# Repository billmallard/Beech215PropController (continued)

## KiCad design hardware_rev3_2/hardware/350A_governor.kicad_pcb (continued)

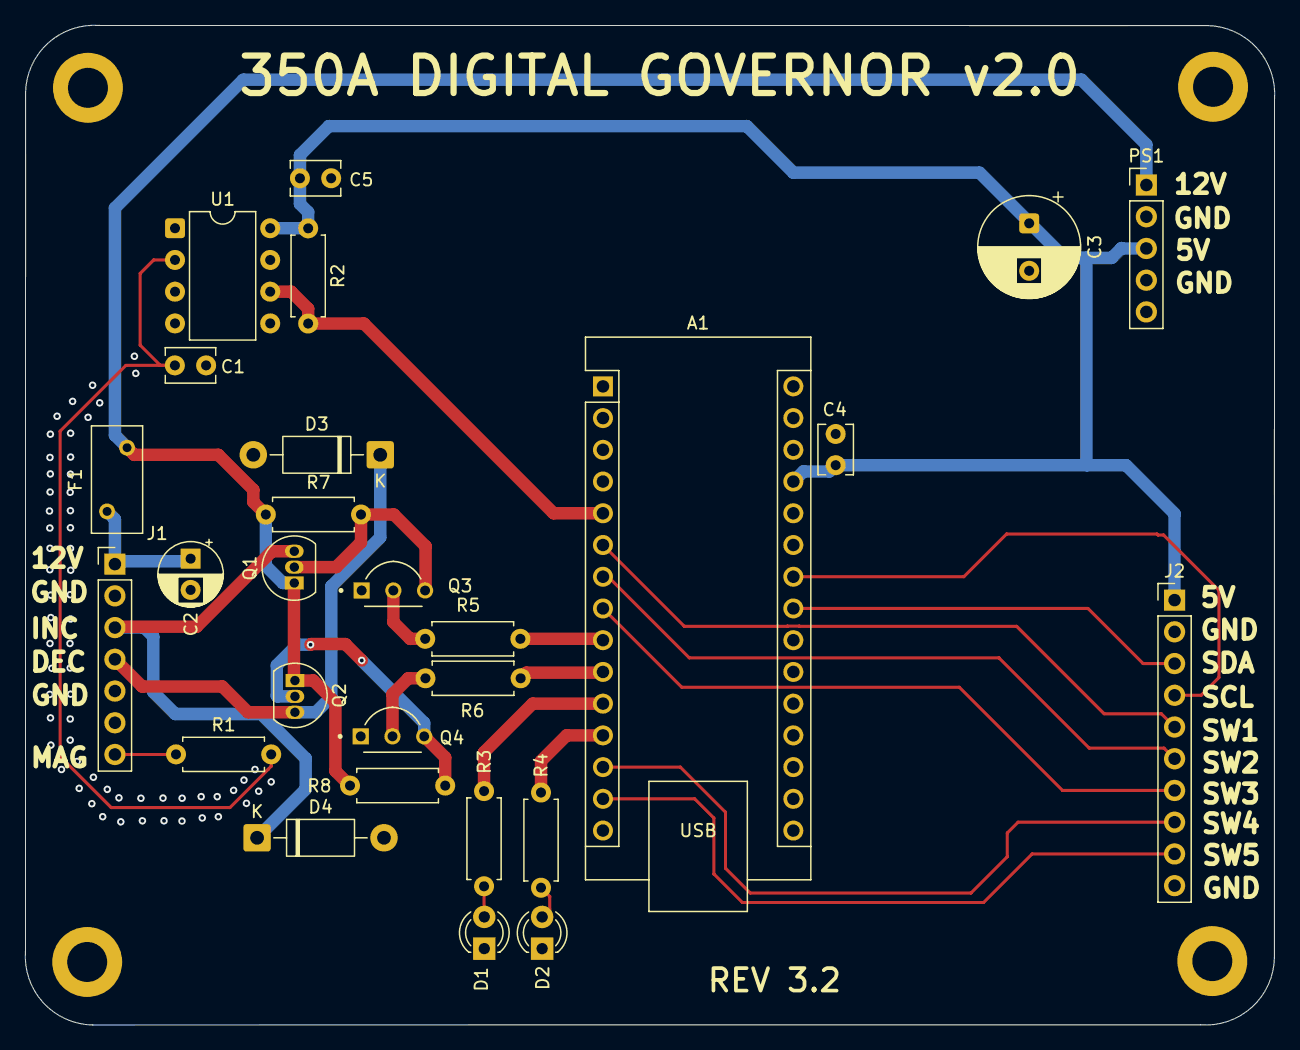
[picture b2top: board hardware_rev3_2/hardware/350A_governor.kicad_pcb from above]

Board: 2 copper layers, 100.0 x 80.0 mm, 27 parts (0 on the bottom side), 26 nets.

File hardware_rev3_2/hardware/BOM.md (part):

# Bill of Materials — Rev 3.2

Complete parts list for one governor build. All parts available from Digi-Key, Mouser, or Amazon.
Links are to Digi-Key where possible — they're reliable, stock everything, and ship fast.

**Estimated total cost: $60–100** depending on sourcing (Amazon vs. Digi-Key, bulk vs. singles)

---

## PCB

| Item | Specification | Qty | Source | Est. Cost | Notes |
|---|---|---|---|---|---|
| Governor PCB | 100×80mm 2-layer FR4 | 5 | JLCPCB | ~$2 + shipping | Upload `gerbers/350A_governor_JLCPCB.zip`; default settings; you get 5, use 1 |

**JLCPCB order settings:**
- Base Material: FR4
- Layers: 2
- PCB Thickness: 1.6mm
- Surface Finish: HASL (with lead) — cheapest and fine for this application
- Copper Weight: 1oz
- Everything else: defaults

---

## ICs and Active Components

| Ref | Part | Description | Digi-Key PN | Qty | Est. Cost | Notes |
|---|---|---|---|---|---|---|
| A1 | Arduino Nano (ATmega328P) | Microcontroller | — | 1 | $4–8 | Buy the CH340 version (most common on Amazon/eBay). Avoid Nano Every — different pinout. |
| U1 | 6N137 | High-speed optocoupler | 516-2878-5-ND | 1 | $0.60 | DIP-8. Do not substitute 4N25/4N35 — too slow for mag pulses. |
| PS1 | LM2596S-5V Module | DC-DC 5V switching regulator | — | 1 | $1–3 | Pre-built module. **Must be labeled "5V" not adjustable.** Verify output before installing. Available on Amazon, 10-packs for $8. |
| OLED | SSD1306 1.3" OLED | I2C display 128×64 | — | 1 | $6–10 | Must be I2C (2-wire), 128×64. Many on Amazon. Verify module is 4-pin (VCC/GND/SCL/SDA). |

---

## Transistors — High-Side Relay Driver

Two-channel NPN+PNP circuit replacing the ULN2003A from Rev 2. All TO-92 package.

| Ref | Part | Type | Digi-Key PN | Qty | Est. Cost | Notes |
|---|---|---|---|---|---|---|
| Q1, Q2 | 2N2907A | PNP — high-side switch | 2N2907A-ND | 2 | ~$0.50 ea | TO-92L. Switches +12V to relay coil. |
| Q3, Q4 | 2N2222A | NPN — level shifter | 2N2222A-ND | 2 | ~$0.30 ea | TO-92. Driven by Nano 5V logic. |

---

## Passives — Resistors

All resistors: 1/4W metal film, 1% tolerance

| Ref | Value | Digi-Key PN | Qty | Notes |
|---|---|---|---|---|
| R1 | 10kΩ | 10KEBK-ND | 1 | Magneto input current limit |
| R2 | 4.7kΩ | 4.7KEBK-ND | 1 | Optocoupler pull-up |
| R3, R4 | 330Ω | 330EBK-ND | 2 | LED current limiters |
| R5, R6 | 1kΩ | 1.0KEBK-ND | 2 | NPN base resistors (Q3, Q4) |
| R7, R8 | 10kΩ | 10KEBK-ND | 2 | PNP base pull-up to +12V (Q1, Q2) |

**Tip:** R1, R7, R8 are all 10kΩ — order 4 total on a single line item.

---

## Passives — Capacitors

| Ref | Value | Type | Digi-Key PN | Qty | Notes |
|---|---|---|---|---|---|
| C1, C4, C5 | 100nF (0.1µF) | Ceramic disc | 445-173-ND | 3 | Non-polarized; marked "104" |
| C2 | 100µF 25V | Electrolytic | 493-1215-ND | 1 | **POLARIZED** — observe polarity. 12V input bulk cap. |
| C3 | 47µF 10V | Electrolytic | 493-1205-ND | 1 | **POLARIZED** — observe polarity. 5V output filter cap. |

---

## Protection — Diodes and Fuse

| Ref | Part | Digi-Key PN | Qty | Notes |
|---|---|---|---|---|
| D3, D4 | 1N4001 | 1N4001FSCT-ND | 2 | Flyback diodes across each relay coil circuit — clamp the coil's inductive spike when the PNP switches off. **Do not omit.** Polarity: cathode (band) to the relay output pad (marked "K" on silkscreen), anode to ground. |
| F1 | 1A PTC resettable fuse | — | 1 | In series with +12V_RAW input. Self-resets after overcurrent. Belkin/Bel Fuse 0ZRE or equivalent. |

---

## Indicators

| Ref | Part | Digi-Key PN | Qty | Notes |
|---|---|---|---|---|
| D1 | 3mm Red LED | 754-1264-ND | 1 | Standard brightness; INC indicator |
| D2 | 3mm Green LED | 754-1221-ND | 1 | Standard brightness; DEC indicator |

---

## Connectors and Sockets

| Ref | Part | Qty | Notes |
|---|---|---|---|
| — | DIP-8 socket | 1 | For U1 (6N137). Use machined-pin (turned-pin) type for reliability. |
| — | 15-pin female single-row socket strip | 2 | For Arduino Nano. Cut to length or buy pre-cut Nano socket kit. |
| J1 | 1×7 2.54mm male header | 1 | 7-pin aircraft interface connector; or cut from 40-pin strip |
| J2 | 1×10 2.54mm male header | 1 | 10-pin panel unit connector; or cut from 40-pin strip |
| PS1 | 1×5 2.54mm male header | 1 | 5-pin for LM2596 module |
| — | 40-pin 2.54mm male header strip | 1 | Break-apart; covers J1/J2/PS1 (22 pins needed) |

**Tip:** Buy a 40-pin break-apart header strip and a 40-pin female socket strip on Amazon (~$1 each). These cover all connector needs on the board.

---

## Panel Unit Components

| Part | Qty | Est. Cost | Notes |
|---|---|---|---|
| 5-position rotary switch | 1 | $8–15 | **Single-pole, 5-position.** Lorlin CK1024 or Grayhill 56-series. Must have positive detents (not a continuous encoder). Panel-mount with standard ¼" shaft. |
| Project enclosure or panel plate | 1 | $5–15 | Size depends on your panel opening. Aluminum preferred. |
| Multi-conductor shielded cable | ~3 ft | $5–10 | 10 conductors sufficient. Belden 9536 or equivalent avionics-grade cable. |

**Switch selection notes:**
- Lorlin CK1024: 12-position base type, order 5-position variant. Available Mouser/Digi-Key. ~$8.
- Grayhill 56-series: industry-standard panel switch, very positive detent feel, standard ¼" D-shaft. ~$12–15.
- Avoid: continuous rotary encoders (no detents), wafer switches without detents, or switches with more than 5 positions (firmware only uses 5).
- The original prop control knob reuses directly on any ¼" D-shaft switch.

---

## Aircraft Interface

| Part | Qty | Source | Notes |
|---|---|---|---|
| 7-pin Cannon/MS connector (plug) | 1 | Aircraft Spruce, B&C Specialty, Stein Air | MS3106A-16-10S or equivalent. Match to existing connector on airframe. **Measure yours first.** ~$15–40 |
| Backshell for connector | 1 | Same sources | Strain relief; important for vibration environment |
| 22 AWG shielded wire | ~2 ft | Aircraft Spruce or local | For magneto lead connection inside governor box |
| Heat shrink tubing assortment | 1 | — | Cover all solder connections |
| Aluminum project box | 1 | Hammond Mfg or similar | Size your own governor box; original dimensions ~85×65×30mm |

---

## Tools Required (not included in cost estimate)

- Temperature-controlled soldering iron
- Multimeter
- Flush cutters
- Arduino IDE (free download)
- USB-A cable for programming Nano
- Oscilloscope (recommended but optional)
- Second Arduino Nano for bench test pulse generator (~$5 extra)

---

## Complete Order Summary

### Digi-Key single order (all board passives + ICs):
6N137 × 1, 2N2907A × 2, 2N2222A × 2, 1N4001 × 2, 10kΩ resistor × 4 (R1/R7/R8 + spare), 4.7kΩ × 1, 1kΩ × 2, 330Ω × 2, 100nF cap × 3, 100µF 25V cap × 1, 47µF 10V cap × 1, DIP-8 socket × 1

**Estimated Digi-Key subtotal: ~$14–20**

### Amazon or eBay (modules and panels):
Arduino Nano × 1, LM2596-5V module × 1, SSD1306 OLED 1.3" × 1, LED assortment (red + green 3mm) × 1, pin header strips × 1, female socket strips × 1, 1A PTC fuse × 1

**Estimated Amazon subtotal: ~$18–28**

### Mouser or Digi-Key (rotary switch):
5-position rotary switch (Lorlin CK1024 or Grayhill 56-series) × 1

**Estimated switch cost: ~$8–15**

### Aircraft Spruce or B&C (aircraft hardware):
7-pin Cannon connector and backshell, avionics wire

**Estimated aircraft hardware: ~$20–45**

### JLCPCB:
5× PCBs + shipping (typically $2 boards + $8–15 shipping to US)

**Estimated PCB: ~$10–17**

---

## Notes on Substitutions

**Arduino Nano:** The CH340 USB chip version is fine. Avoid:
- Arduino Nano Every (different pinout)
- Arduino Nano 33 IoT / BLE (3.3V logic — relay drive levels won't work)
- Any 3.3V variant

**6N137 optocoupler:** Do not substitute with slower optocouplers (4N25, 4N35, PC817). The magneto signal at cruise RPM is ~130 Hz and the pulse width matters. The 6N137 has 10ns response time — slower types will miss pulses or distort the signal.

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
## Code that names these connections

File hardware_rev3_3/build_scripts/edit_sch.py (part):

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label('VCC5', 110.49, 167.64, 0)

# PNP base nets get their own names (series base resistor goes between)
t = relabel(t, 'Q3_COLL', '223.52 140.97', 'Q1_BASE')
t = relabel(t, 'Q4_COLL', '222.25 200.66', 'Q2_BASE')
# magneto series resistor split in two
t = relabel(t, 'MAG_FILT', '34.29 185.42', 'MAG_MID')
t = set_prop(t, 'R1', 'Value', '10k', '5k1')
# bulk cap moves behind the fuse
t = relabel(t, '12V_IN', '88.9 68.58', '12V_RAW')
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    t = set_prop(t, q, 'Footprint', 'Package_TO_SOT_THT:TO-92L_Inline', 'Package_TO_SOT_THT:TO-92L_Inline_Wide')

# J1: E = pot high side, F = pot return (GND)
t = relabel(t, 'GND', '48.26 74.93', 'POT_HI')
label('GND', 48.26, 77.47, 0)
t = set_prop(t, 'J1', 'Footprint', 'PinHeader_1x07_P2.54mm_Vertical', 'Governor:PinHeader_1x07_P2.54mm_Vertical_Pin7Offset')

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# PNP base series resistors (the missing current limit)
r_horiz('R11', '1k', 223.52, 152.4)
wire(219.71, 152.4, 214.63, 152.4)
label('Q3_COLL', 214.63, 152.4, 180)
wire(227.33, 152.4, 227.33, 140.97)
junction(227.33, 140.97)
r_horiz('R13', '1k', 223.52, 212.09)
wire(219.71, 212.09, 214.63, 212.09)
label('Q4_COLL', 214.63, 212.09, 180)
wire(227.33, 212.09, 227.33, 200.66)
junction(227.33, 200.66)

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wire(g(230), g(130), g(230), g(132))
junction(g(230), g(132))
wire(g(230), g(132), g(222), g(132))
label('POT_HI', g(222), g(132), 180)
wire(g(230), g(132), g(235), g(132))
r_horiz('R19', '10k', g(238), g(132))
wire(g(241), g(132), g(250), g(132))
label('POT_SENSE', g(250), g(132), 0)
c_vert('C6', '100nF', g(246), g(137))
wire(g(246), g(134), g(246), g(132))
junction(g(246), g(132))
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# --- magneto input box
rect(g(266), g(155), g(310), g(205))
note('MAG INPUT (2nd series R, LED reverse clamp)', g(288), g(158), 1.6)
label('MAG_MID', g(274), g(172), 180)
wire(g(274), g(172), g(279), g(172))
r_horiz('R9', '5k1', g(282), g(172))
wire(g(285), g(172), g(300), g(172))
label('MAG_FILT', g(300), g(172), 0)
d_vert('D6', '1N4148', g(292), g(177), 'Diode_THT:D_DO-35_SOD27_P7.62mm_Horizontal', 'Diode:1N4148')
wire(g(292), g(174), g(292), g(172))
junction(g(292), g(172))
gndw(g(292), g(180))

# Nano analog inputs
label('INC_SENSE', 204.47, 77.47, 0)
label('DEC_SENSE', 204.47, 85.09, 0)
label('POT_SENSE', 204.47, 87.63, 0)

# explicit no-connects on pins that are intentionally unused
for xy in ((179.07, 54.61), (179.07, 57.15), (179.07, 62.23), (179.07, 64.77), (179.07, 67.31), (179.07, 80.01),
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
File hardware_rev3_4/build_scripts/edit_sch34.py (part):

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

# Q6 level shifter, driven from Nano D5
label('D5_DRV_EN', gx(30), g(190), 180)
wire((gx(30), g(190)), (gx(34), g(190)))
r_vert('R25', '10k', gx(32), g(195))
wire((gx(32), g(192)), (gx(32), g(190)))
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label('12V_SW', gx(72), g(192), 270)
r_horiz('R26', '33k', gx(79), g(188))
wire((gx(82), g(188)), (gx(92), g(188)))
label('SW_SENSE', gx(92), g(188), 0)
r_vert('R27', '10k', gx(87), g(193))
wire((gx(87), g(190)), (gx(87), g(188)))
junction(gx(87), g(188))
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                       + j3[m.end():])
# pin 1 (g233, g30) -> R28 -> 12 V rail
wire((g(233), g(30)), (g(240), g(30)))
label('LAMP_P', g(234), g(30), 0)
r_horiz('R28', '1k', g(243), g(30), R_FP_WIDE, dnp=True)
wire((g(246), g(30)), (g(250), g(30)))
label('12V_RAW', g(250), g(30), 0)
# pin 2 (g233, g32) -> R29 -> Q7 collector
wire((g(233), g(32)), (g(235), g(32)), (g(235), g(38)), (g(240), g(38)))
label('LAMP_N', g(235), g(38), 180)
r_horiz('R29', '1k', g(243), g(38), dnp=True)
wire((g(246), g(38)), (g(255), g(38)), (g(255), g(42)))
npn('Q7', g(253), g(46), dnp=True)
gndw(g(255), g(50))
# D4 -> R30 -> Q7 base, R31 pull-down
label('D4_FAULT', g(233), g(46), 180)
wire((g(233), g(46)), (g(242), g(46)))
r_vert('R31', '10k', g(237), g(51), dnp=True)
wire((g(237), g(48)), (g(237), g(46)))
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
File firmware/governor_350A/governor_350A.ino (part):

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
// ── HARDWARE PINS ─────────────────────────────────────────────────────────────
#define PIN_RPM_INPUT   2   // 6N137 output -> INT0 (hardware interrupt)
#define PIN_INC_RELAY   6   // NPN base (via 1k) -> PNP high-side switch -> INC RPM relay (fine pitch)
#define PIN_DEC_RELAY   7   // NPN base (via 1k) -> PNP high-side switch -> DEC RPM relay (coarse pitch)
#define PIN_INC_LED     8   // Red LED — INC activity indicator
#define PIN_DEC_LED     9   // Green LED — DEC activity indicator
#define PIN_POT         A7  // Panel pot sense (analog-only pin)
// Relay output readback (33k/10k dividers) — see OUTPUT DRIVER READBACK below.
#define PIN_INC_SENSE   A3  // INC_RELAY output / 4.3
#define PIN_DEC_SENSE   A6  // DEC_RELAY output / 4.3 (analog-only pin)
// A4 = SDA, A5 = SCL — optional OLED on the 4-pin service header (Wire library)
#define PIN_DRV_EN      5   // Series switch (Q6 -> Q5): HIGH = relay drivers powered
#define PIN_SW_SENSE    A2  // 12V_SW (after the series switch) / 4.3
#define PIN_FAULT_LAMP  4   // Optional fault lamp (J3, not fitted by default): HIGH = lit
// D3, D10, D11 are unconnected and are left as inputs with pull-ups.

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  uint32_t    mismatchSince_ms;
  DriverFault fault;             // STUCK_ON on a relay output trips; everything else is report only
};
DriverMon incDrv = { PIN_INC_SENSE, false, 0, false, 0, DRV_OK };
DriverMon decDrv = { PIN_DEC_SENSE, false, 0, false, 0, DRV_OK };
DriverMon swDrv  = { PIN_SW_SENSE,  false, 0, false, 0, DRV_OK };   // the series switch
// Set when a relay output is found live while commanded off. Cleared only by
// a reset, i.e. by cycling power. The series switch stays open meanwhile.
bool     driverTripped = false;
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  uint32_t now = millis();
  if (inc != incDrv.cmd) { incDrv.cmd = inc; incDrv.change_ms = now; }
  if (dec != decDrv.cmd) { decDrv.cmd = dec; decDrv.change_ms = now; }
  if (!inc) { digitalWrite(PIN_INC_RELAY, LOW);  digitalWrite(PIN_INC_LED, LOW);  }
  if (!dec) { digitalWrite(PIN_DEC_RELAY, LOW);  digitalWrite(PIN_DEC_LED, LOW);  }
  if (inc)  { digitalWrite(PIN_INC_RELAY, HIGH); digitalWrite(PIN_INC_LED, HIGH); }
  if (dec)  { digitalWrite(PIN_DEC_RELAY, HIGH); digitalWrite(PIN_DEC_LED, HIGH); }
}

void relayOff() {
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  Serial.print(F("RAMP_RATE=")); Serial.print(RAMP_RATE_RPM_PER_SEC); Serial.println(F(" RPM/sec"));

  // Output pins — relay channels drive NPN+PNP high-side switches; HIGH = relay on
  pinMode(PIN_INC_RELAY, OUTPUT); digitalWrite(PIN_INC_RELAY, LOW);
  pinMode(PIN_DEC_RELAY, OUTPUT); digitalWrite(PIN_DEC_RELAY, LOW);
  pinMode(PIN_INC_LED,   OUTPUT); digitalWrite(PIN_INC_LED,   LOW);
  pinMode(PIN_DEC_LED,   OUTPUT); digitalWrite(PIN_DEC_LED,   LOW);
  // Series switch open and fault lamp off until the checks below
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  incDrv.mismatch = decDrv.mismatch = swDrv.mismatch = false;
  setSwitch(false);
  delay(SENSE_SETTLE_MS);
  if (senseHigh(PIN_SW_SENSE)) {
    swDrv.fault = DRV_STUCK_ON;
    Serial.println(F("DRIVER SW: STUCK_ON (series switch cannot open)"));
  }
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
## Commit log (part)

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2026-03-09 Updated engine pulse table
2026-03-09 File cleanup
2026-03-09 Reorg files
2026-03-09 Change in switch architecture
2026-03-09 Readme cleanup
2026-03-12 Fiverr design.
2026-03-12 Latest spec document
2026-03-13 Project cleanup
2026-04-11 Updated BOM with shopping lists
2026-04-12 Secret detection
2026-04-12 Build changes
2026-04-14 PCB Revisions after changes suggested
2026-04-20 Latest PCB version
2026-04-27 Rev 3 Hardware Delivery and name changes
2026-04-27 Rev 3_1 PCB and project lcleanup
2026-04-27 Build cleanup
2026-04-27 More cleanup
2026-04-27 Updated schematic
2026-04-27 Cleanup and .gitignore changes
2026-04-27 Deleting more stale files
2026-04-27 Updating documentation.
